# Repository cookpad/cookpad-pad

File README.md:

# Cookpad Pad 2

A six keys macro pad made by Cookpad.

## Firmware

Clone [forked QMK](https://github.com/takai/qmk_firmware/tree/cookpad-pad2) repositories and setup build environment.
Then type following command:

```
$ make cookpad_pad:default:dfu
```

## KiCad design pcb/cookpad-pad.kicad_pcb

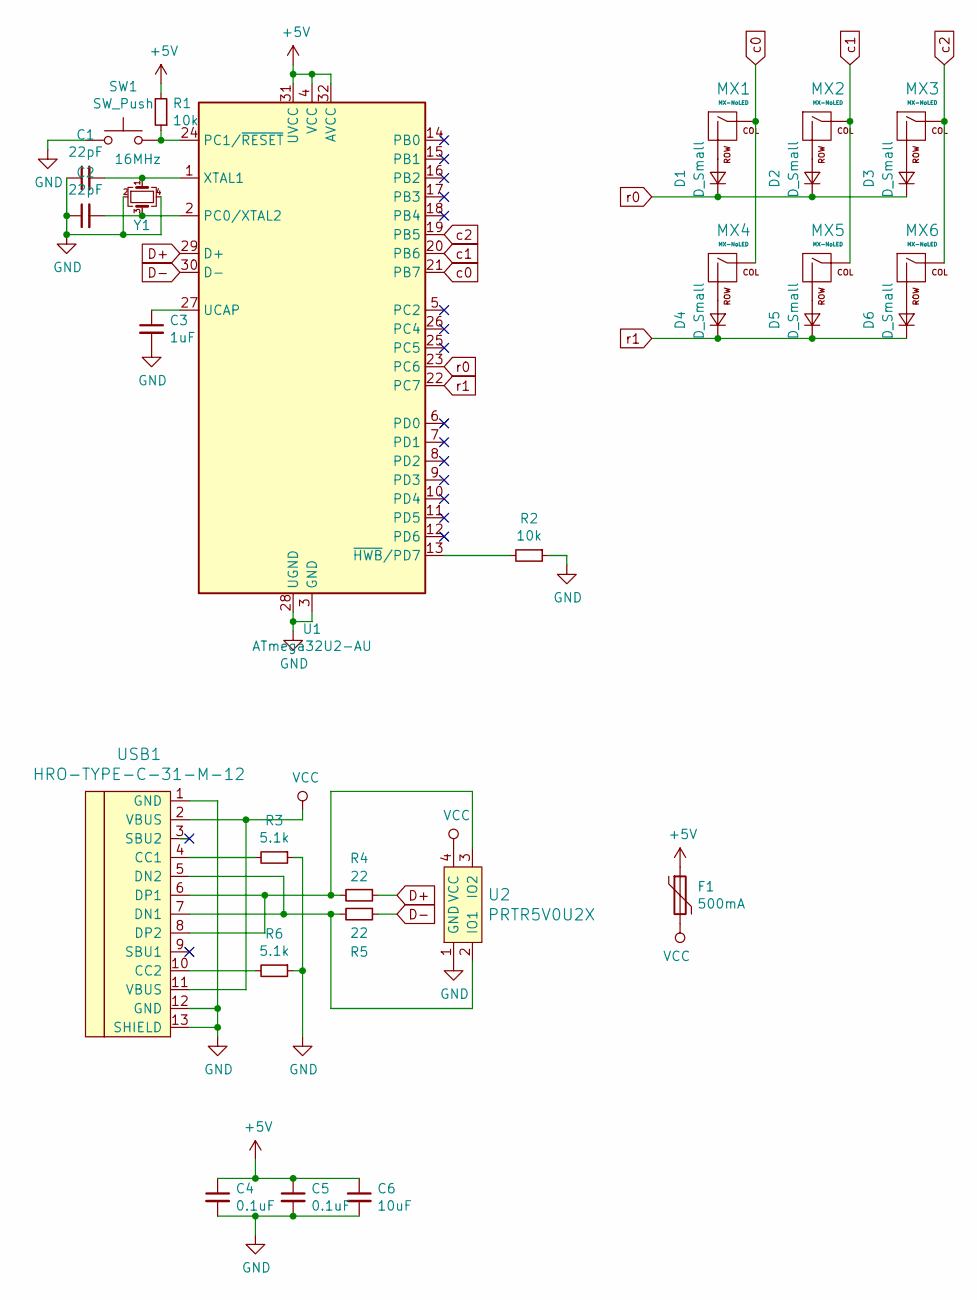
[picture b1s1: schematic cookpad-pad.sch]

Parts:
C1, C2: 22pF; C_0603_1608Metric
C3: 1uF; C_0603_1608Metric
C4, C5: 0.1uF; C_0603_1608Metric
C6: 10uF; C_0603_1608Metric
D1, D2, D3, D4, D5, D6: D_Small; D_SOD-123
F1: 500mA; Fuse_1206_3216Metric
MX1, MX2, MX3, MX4, MX5, MX6: MX-NoLED; MXOnly-1U-NoLED
R1, R2: 10k; R_0805_2012Metric
R3, R6: 5.1k; R_0805_2012Metric
R4, R5: 22; R_0805_2012Metric
SW1: SW_Push; SKQG-1155865
U1: ATmega32U2-AU; TQFP-32_7x7mm_P0.8mm
U2: PRTR5V0U2X; SOT143B
USB1: HRO-TYPE-C-31-M-12; HRO-TYPE-C-31-M-12-Assembly
Y1: 16MHz; Crystal_SMD_3225-4Pin_3.2x2.5mm

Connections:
+5V: C4.1, C5.1, C6.1, F1.1, R1.2, U1.4 (VCC), U1.31 (UVCC), U1.32 (AVCC)
D+: R4.1, U1.29 (D+)
D-: R5.1, U1.30 (D-)
GND: C1.1, C2.1, C3.2, C4.2, C5.2, C6.2, R2.1, R3.1, R6.1, SW1.1, U1.3 (GND), U1.28 (UGND), U2.1 (GND), USB1.1 (GND), USB1.12 (GND), USB1.13 (SHIELD), Y1.2, Y1.4
unnamed: C1.2, U1.1 (XTAL1), Y1.1
unnamed: C2.2, U1.2 (PC0/XTAL2), Y1.3
unnamed: C3.1, U1.27 (UCAP)
unnamed: D1.2 (A), MX1.2 (ROW)
unnamed: D2.2 (A), MX2.2 (ROW)
unnamed: D3.2 (A), MX3.2 (ROW)
unnamed: D4.2 (A), MX4.2 (ROW)
unnamed: D5.2 (A), MX5.2 (ROW)
unnamed: D6.2 (A), MX6.2 (ROW)
unnamed: R1.1, SW1.2, U1.24 (PC1/~RESET)
unnamed: R2.2, U1.13 (~HWB~/PD7)
unnamed: R3.2, USB1.4 (CC1)
unnamed: R4.2, U2.3 (IO2), USB1.6 (DP1), USB1.8 (DP2)
unnamed: R5.2, U2.2 (IO1), USB1.5 (DN2), USB1.7 (DN1)
unnamed: R6.2, USB1.10 (CC2)
VCC: F1.2, U2.4 (VCC), USB1.2 (VBUS), USB1.11 (VBUS)
c0: MX1.1 (COL), MX4.1 (COL), U1.21 (PB7)
c1: MX2.1 (COL), MX5.1 (COL), U1.20 (PB6)
c2: MX3.1 (COL), MX6.1 (COL), U1.19 (PB5)
r0: D1.1 (K), D2.1 (K), D3.1 (K), U1.23 (PC6)
r1: D4.1 (K), D5.1 (K), D6.1 (K), U1.22 (PC7)

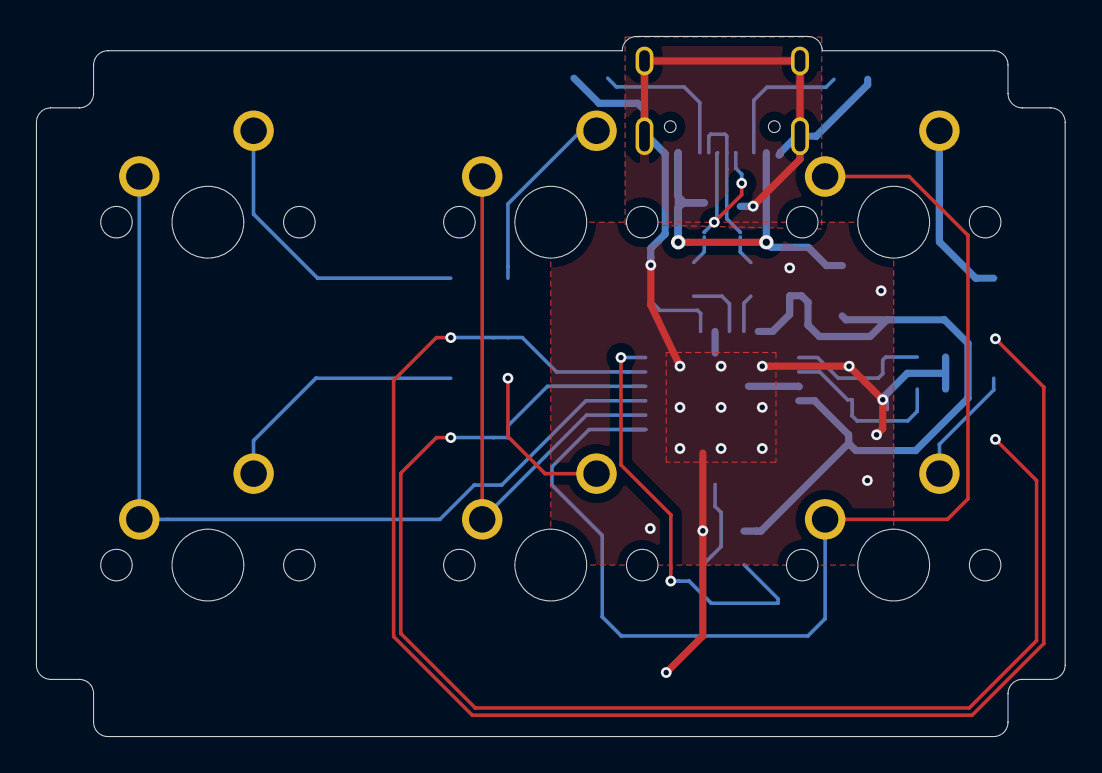
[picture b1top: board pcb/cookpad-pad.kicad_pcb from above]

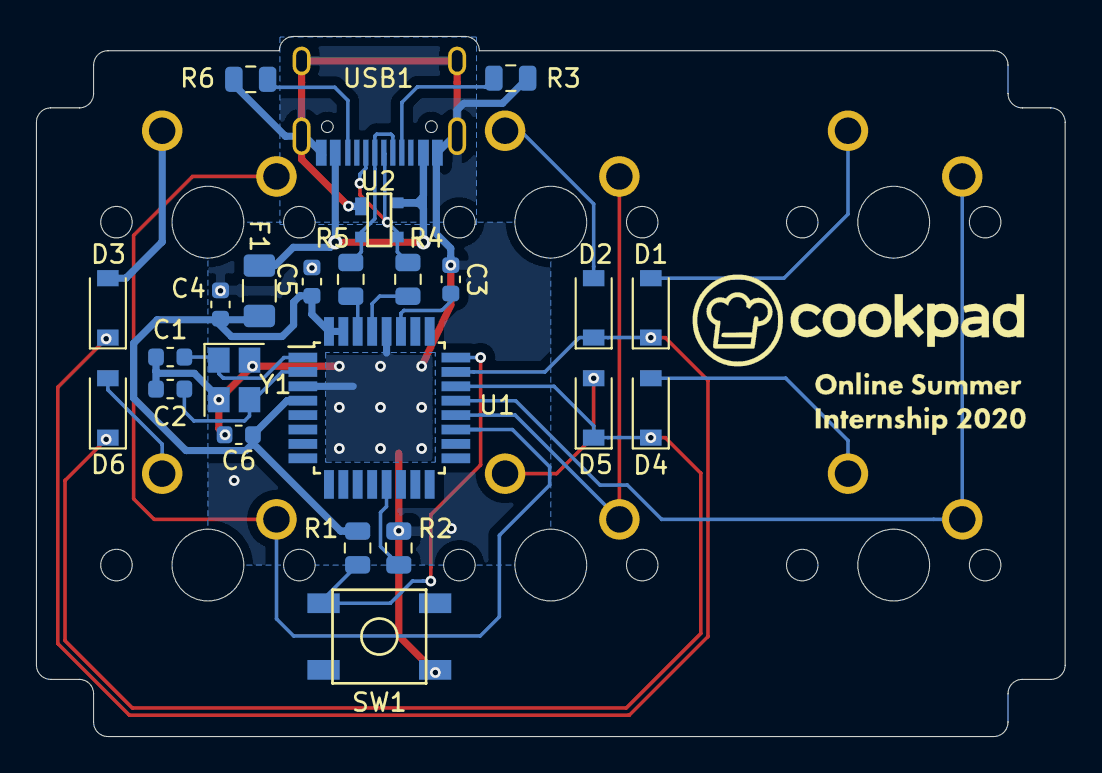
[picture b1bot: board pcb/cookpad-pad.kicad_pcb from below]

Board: 2 copper layers, 57.2 x 38.9 mm, 30 parts (24 on the bottom side), 25 nets.

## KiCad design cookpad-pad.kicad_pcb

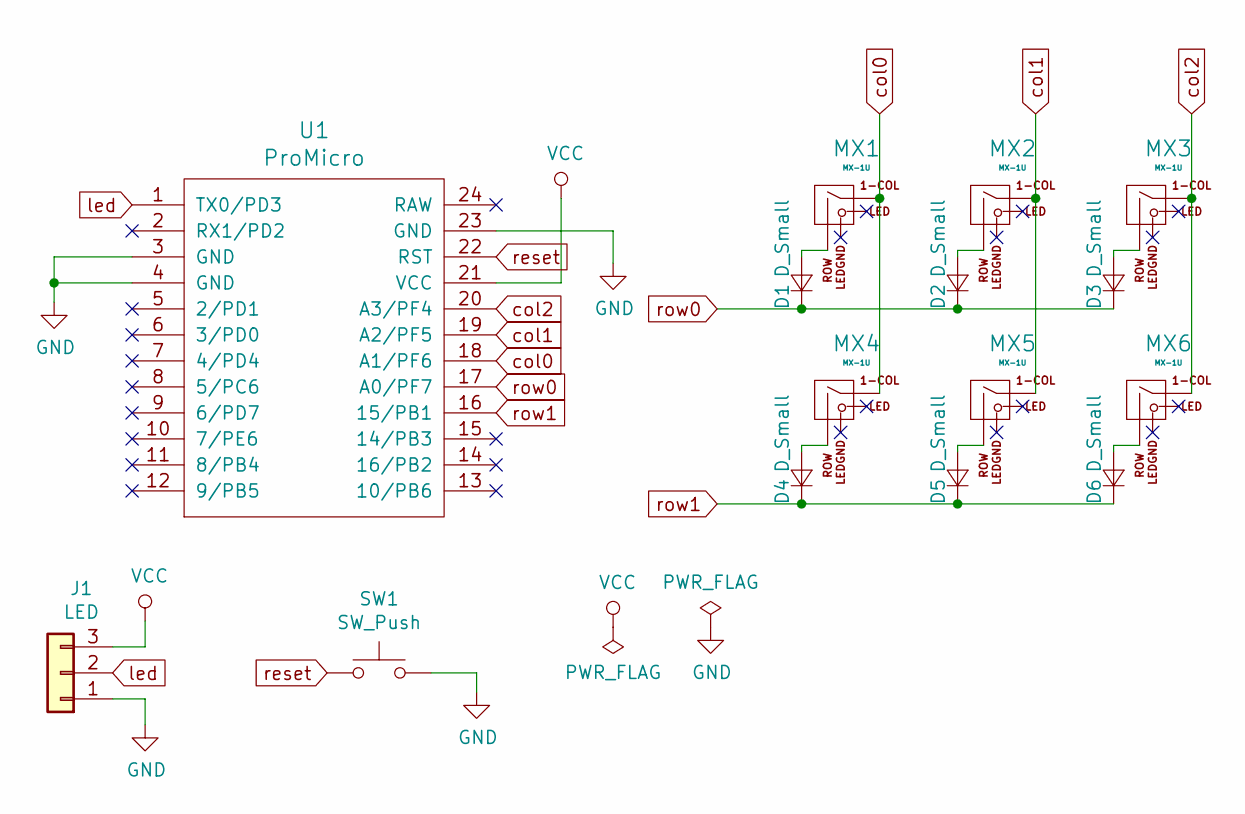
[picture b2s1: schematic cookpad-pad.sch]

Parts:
D1, D2, D3, D4, D5, D6: D_Small; D3_TH_SMD
J1: LED; LED_Strip
MX1, MX2, MX3, MX4, MX5, MX6: MX-1U; MXOnly-1U-NoLED
SW1: SW_Push; ResetSW
U1: ProMicro; ArduinoProMicro-TopSide

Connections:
GND: J1.1, SW1.2, U1.3 (GND), U1.4 (GND), U1.23 (GND)
unnamed: D1.2 (A), MX1.2 (ROW)
unnamed: D2.2 (A), MX2.2 (ROW)
unnamed: D3.2 (A), MX3.2 (ROW)
unnamed: D4.2 (A), MX4.2 (ROW)
unnamed: D5.2 (A), MX5.2 (ROW)
unnamed: D6.2 (A), MX6.2 (ROW)
VCC: J1.3, U1.21 (VCC)
col0: MX1.1 (COL), MX4.1 (COL), U1.18 (A1/PF6)
col1: MX2.1 (COL), MX5.1 (COL), U1.19 (A2/PF5)
col2: MX3.1 (COL), MX6.1 (COL), U1.20 (A3/PF4)
led: J1.2, U1.1 (TX0/PD3)
reset: SW1.1, U1.22 (RST)
row0: D1.1 (K), D2.1 (K), D3.1 (K), U1.17 (A0/PF7)
row1: D4.1 (K), D5.1 (K), D6.1 (K), U1.16 (15/PB1)

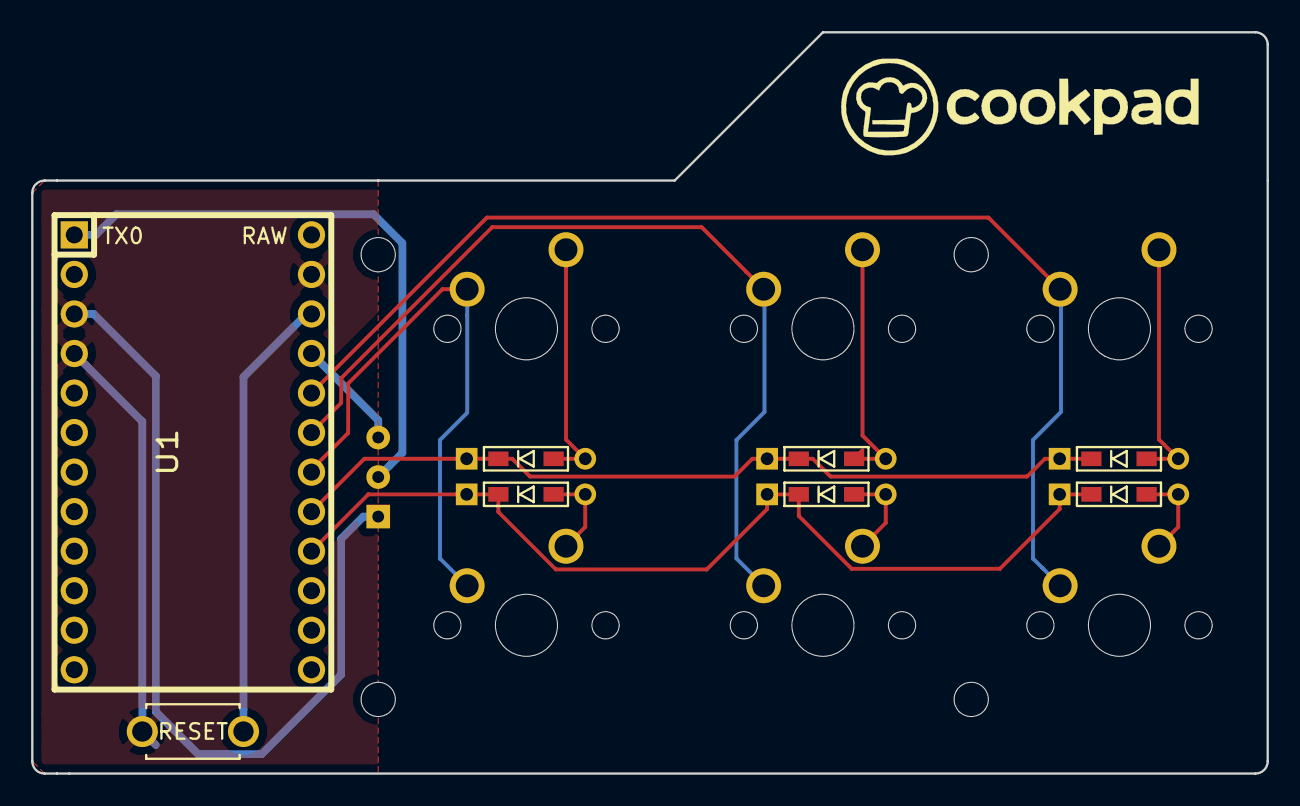
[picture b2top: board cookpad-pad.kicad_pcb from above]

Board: 2 copper layers, 79.4 x 47.6 mm, 15 parts (0 on the bottom side), 15 nets.

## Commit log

2019-01-23 Initialize project
2019-01-23 Add submodules
2019-01-23 Add KiCad files
2019-01-23 Add more spaces for indenting
2019-01-24 Update PCB
2019-04-07 Add images
2019-04-07 Add Japanese build guide
2019-05-05 The reset switch and pin-headers are placed on 表面
2020-09-10 New version of Cookpad Pad
2020-09-10 Add pcb
2020-09-10 Add plate files
2020-09-10 Add files for production
2020-09-10 Add build guide
2020-09-14 Update NOTICE
